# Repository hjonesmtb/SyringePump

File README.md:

# SyringePump

datasheet: https://www.harvardapparatus.com/media/harvard/pdf/552222_Pump_22_Manual.pdf

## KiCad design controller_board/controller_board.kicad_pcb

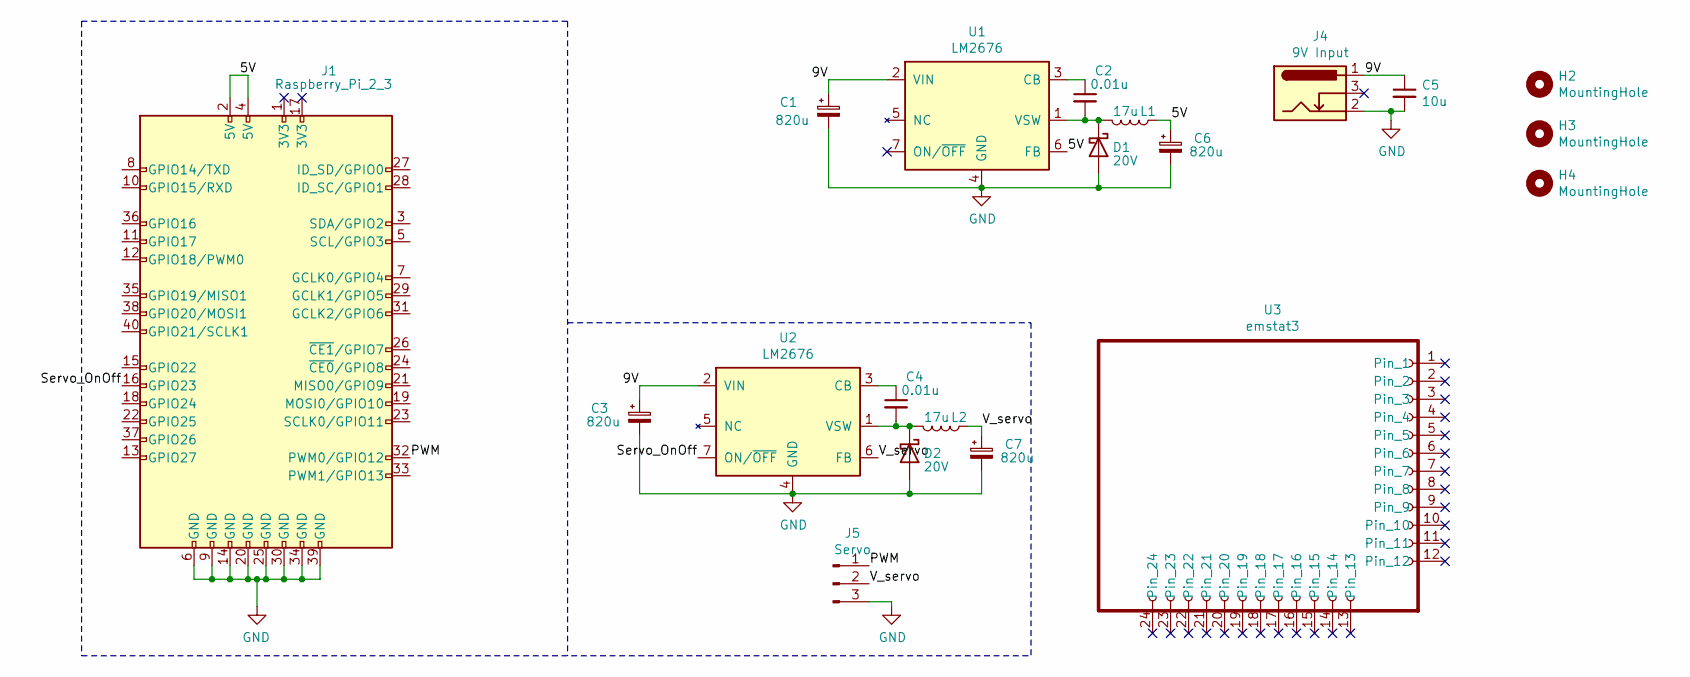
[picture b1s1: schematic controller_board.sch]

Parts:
C1, C3, C6, C7: 820u; CP_Radial_D12.5mm_P5.00mm
C2, C4: 0.01u; C_Rect_L4.0mm_W2.5mm_P2.50mm
C5: 10u; CP_Radial_D4.0mm_P1.50mm
D1, D2: 20V; D_DO-201AD_P12.70mm_Horizontal
H2, H3, H4: MountingHole; MountingHole_2.7mm_M2.5
J1: Raspberry_Pi_2_3; Rpi_4
J4: 9V Input; BarrelJack_CUI_PJ-102AH_Horizontal
J5: Servo; PinSocket_1x03_P2.54mm_Vertical
L1, L2: 17u; HCTI-15-18.0
U1, U2: LM2676
U3: emstat3; Emstat3

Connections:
/5V: C6.1, J1.2 (5V), J1.4 (5V), L1.1, U1.6 (FB)
/9V: C1.1, C3.1, C5.1, J4.1, U1.2 (VIN), U2.2 (VIN)
/PWM: J1.32 (PWM0/GPIO12), J5.1
/Servo_OnOff: J1.16 (GPIO23), U2.7 (ON/~OFF)
/V_servo: C7.1, J5.2, L2.1, U2.6 (FB)
GND: C1.2, C3.2, C5.2, C6.2, C7.2, D1.2 (A), D2.2 (A), J1.6 (GND), J1.9 (GND), J1.14 (GND), J1.20 (GND), J1.25 (GND), J1.30 (GND), J1.34 (GND), J1.39 (GND), J4.2, J5.3, U1.4 (GND), U2.4 (GND)
unnamed: C2.1, U1.3 (CB)
unnamed: C2.2, D1.1 (K), L1.2, U1.1 (VSW)
unnamed: C4.1, U2.3 (CB)
unnamed: C4.2, D2.1 (K), L2.2, U2.1 (VSW)

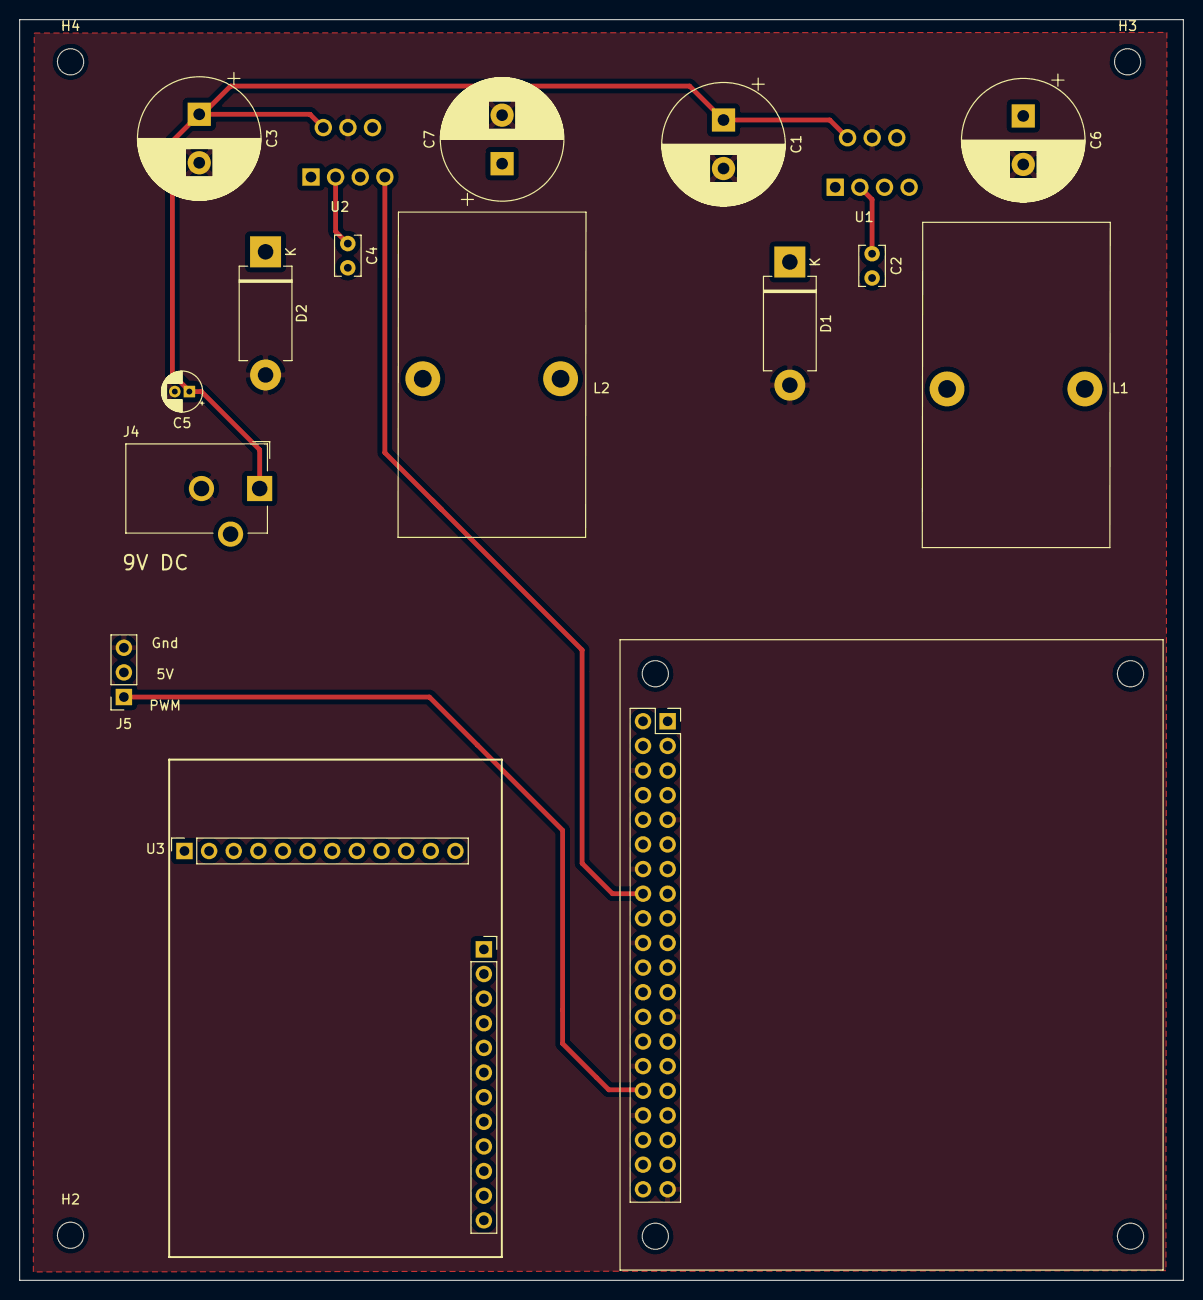
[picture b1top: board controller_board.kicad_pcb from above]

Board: 2 copper layers, 120.0 x 130.0 mm, 20 parts (1 on the bottom side), 10 nets.

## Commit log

2021-12-06 working code for model 22 pump
2021-12-15 added GUI for controlling syringe pump. Pstat not integrated yet.
2022-01-18 Uploaded emstat communication
2022-01-18 Put stuff in respective folders
2022-01-18 added some comments
2022-01-18 added system control for pstat
2022-01-18 integration
2022-01-18 Removed self.ser references
2022-01-23 Debugging done, plots current
2022-01-23 pulling pstat update
2022-01-23 working code with pstat - pump integration
2022-01-23 Current now reading properly
2022-01-24 Resizeable window
2022-01-29 Deposition time now controlled by the flow rate and the deposition step volume
2022-02-07 CSV and plot saving, drop down menu for swv params, test name
2022-02-12 Included port compatability for Linux
2022-02-12 fixed serial import
2022-02-12 fixed error
2022-02-12 drop down in progress
2022-02-17 fixing serial com
2022-02-17 pulling
2022-02-17 changed one parameter
2022-02-17 Cleaned up variables
2022-03-01 testing com
2022-03-08 Refactor
2022-03-08 Refactored System_control
2022-03-13 Changing the deposition mode - bad draft
2022-03-13 Added system_data class
2022-03-13 Threaded system
2022-03-14 New deposition - not complete
2022-03-15 Edited GUI and working on threading
2022-03-15 Hopefully working
2022-03-15 threading
2022-03-15 Working, for chrono then swv
2022-03-20 Presentation Changed
2022-03-20 minor change
2022-03-20 Reworked GUI
2022-03-20 Working
2022-03-20 Working with two graphs
2022-03-22 Added JSON configuration
2022-03-22 factorized conduct_measurements
2022-03-22 Pump uncommented
2022-03-23 Added an extra plot for square wave voltammetry and moved plots to the right, now storing axes in system data instead of passing them through classes
2022-03-23 Test windows start maximized
2022-03-23 Added status bars
2022-03-24 Implemented data plotting and saving in System_Dat
2022-03-24 colouring graphs
2022-03-24 added data folder to .gitignore
2022-03-24 Threading works, but the plot colors are buggy
2022-03-26 Minor bugs
2022-03-26 gui updates
2022-03-26 Finished GUI plotting and saving data
2022-03-26 Wrote swv sequence
2022-03-26 Chronoamp sequence written
2022-03-26 uodated plots
2022-03-26 merging
2022-03-26 ready for test
2022-03-26 events initialized
2022-03-26 Changed the threading idea
2022-03-28 swv test
2022-03-28 Working with threading
2022-03-28 TODO plot colours, take out cyclic, and more!
2022-03-28 First pump through going until user stops
2022-03-28 First flow through continuously plots
2022-03-29 Restart and status button update
2022-03-29 push
2022-03-29 Measurement restart. Need to initialize a new system data object
2022-03-29 plotting
2022-03-29 Pump buttons
2022-03-29 Emstat cycles through frequency, buttons updated
2022-03-29 chrono, and system_contro state updates
2022-03-29 Test L_command
2022-03-29 dep hot fix
2022-03-29 tInt calculated properly
2022-03-30 merge
2022-03-30 Fixed states
2022-03-30 frequency indices changed
2022-03-30 main
2022-03-30 pushed
2022-03-30 Changed buttons
2022-03-31 Frequency changes
2022-03-31 multiple freq plots
2022-03-31 Added deposition frequency input
2022-03-31 doned
2022-03-31 Added cr_min, cr_max and measurei_forward to user inputs
2022-03-31 Equilibration time for deposition working
2022-03-31 Added pump functionality, cleaned up code
2022-04-01 Added default COM port
2022-04-01 Final Push? Config still not tested or working
2022-04-01 Fixed chrono bug
2022-04-01 Changed values to ints
2022-04-01 Converted floats to ints
2022-04-02 One more int updated
2022-04-12 Updated colour scheme
